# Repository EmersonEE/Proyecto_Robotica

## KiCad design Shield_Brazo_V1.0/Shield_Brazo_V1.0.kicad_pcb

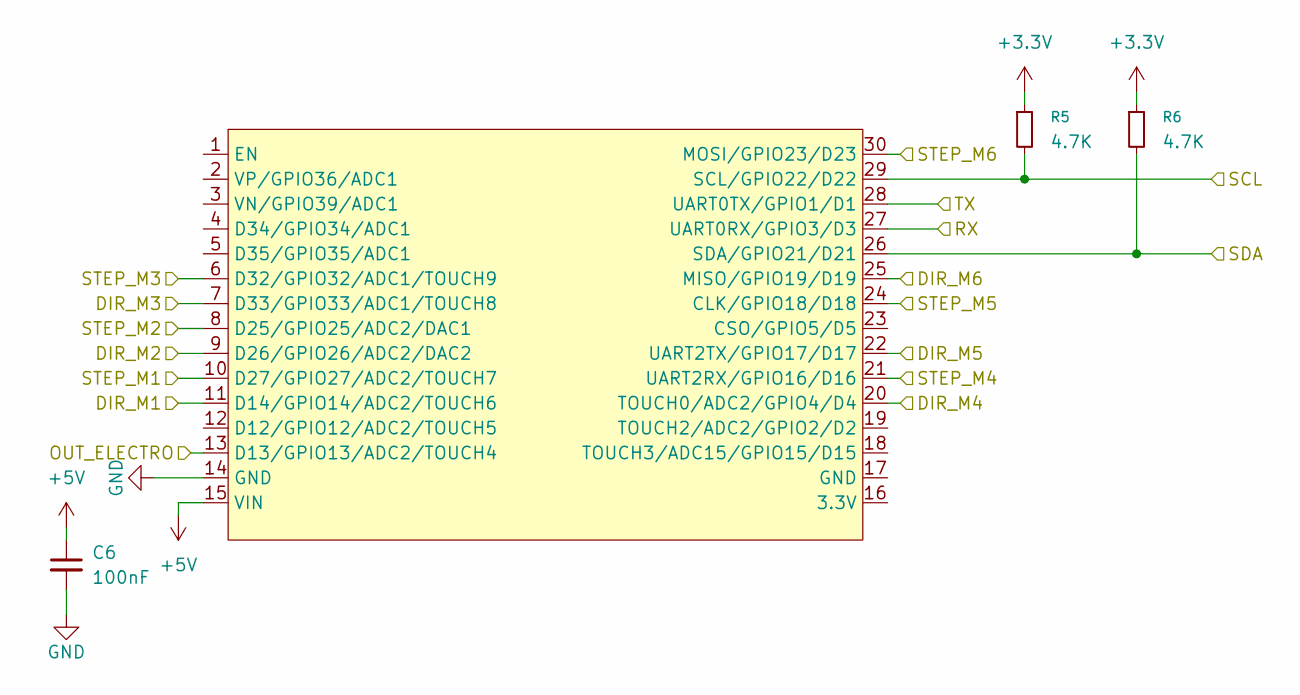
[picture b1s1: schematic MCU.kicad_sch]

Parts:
C6: 100nF; C_1206_3216Metric_Pad1.33x1.80mm_HandSolder
R5, R6: 4.7K
U6: ESP32_DevKit_V1_DOIT; ESP32_DEVKIT_V1_E32

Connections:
+3.3V: R5.1, R6.1; also elsewhere on the board
+5V: C6.1, U6.15 (VIN); also elsewhere on the board
/Drivers/DIR_M1: U6.11 (D14/GPIO14/ADC2/TOUCH6); also elsewhere on the board
/Drivers/DIR_M2: U6.9 (D26/GPIO26/ADC2/DAC2); also elsewhere on the board
/Drivers/DIR_M3: U6.7 (D33/GPIO33/ADC1/TOUCH8); also elsewhere on the board
/Drivers/DIR_M4: U6.20 (TOUCH0/ADC2/GPIO4/D4); also elsewhere on the board
/Drivers/DIR_M5: U6.22 (UART2TX/GPIO17/D17); also elsewhere on the board
/Drivers/DIR_M6: U6.25 (MISO/GPIO19/D19); also elsewhere on the board
/Drivers/STEP_M1: U6.10 (D27/GPIO27/ADC2/TOUCH7); also elsewhere on the board
/Drivers/STEP_M2: U6.8 (D25/GPIO25/ADC2/DAC1); also elsewhere on the board
/Drivers/STEP_M3: U6.6 (D32/GPIO32/ADC1/TOUCH9); also elsewhere on the board
/Drivers/STEP_M4: U6.21 (UART2RX/GPIO16/D16); also elsewhere on the board
/Drivers/STEP_M5: U6.24 (CLK/GPIO18/D18); also elsewhere on the board
/Drivers/STEP_M6: U6.30 (MOSI/GPIO23/D23); also elsewhere on the board
/MCU/OUT_ELECTRO: U6.13 (D13/GPIO13/ADC2/TOUCH4); also elsewhere on the board
/MCU/RX: U6.27 (UART0RX/GPIO3/D3); also elsewhere on the board
/MCU/SCL: R5.2, U6.29 (SCL/GPIO22/D22); also elsewhere on the board
/MCU/SDA: R6.2, U6.26 (SDA/GPIO21/D21); also elsewhere on the board
/MCU/TX: U6.28 (UART0TX/GPIO1/D1); also elsewhere on the board
GND: C6.2, U6.14 (GND); also elsewhere on the board

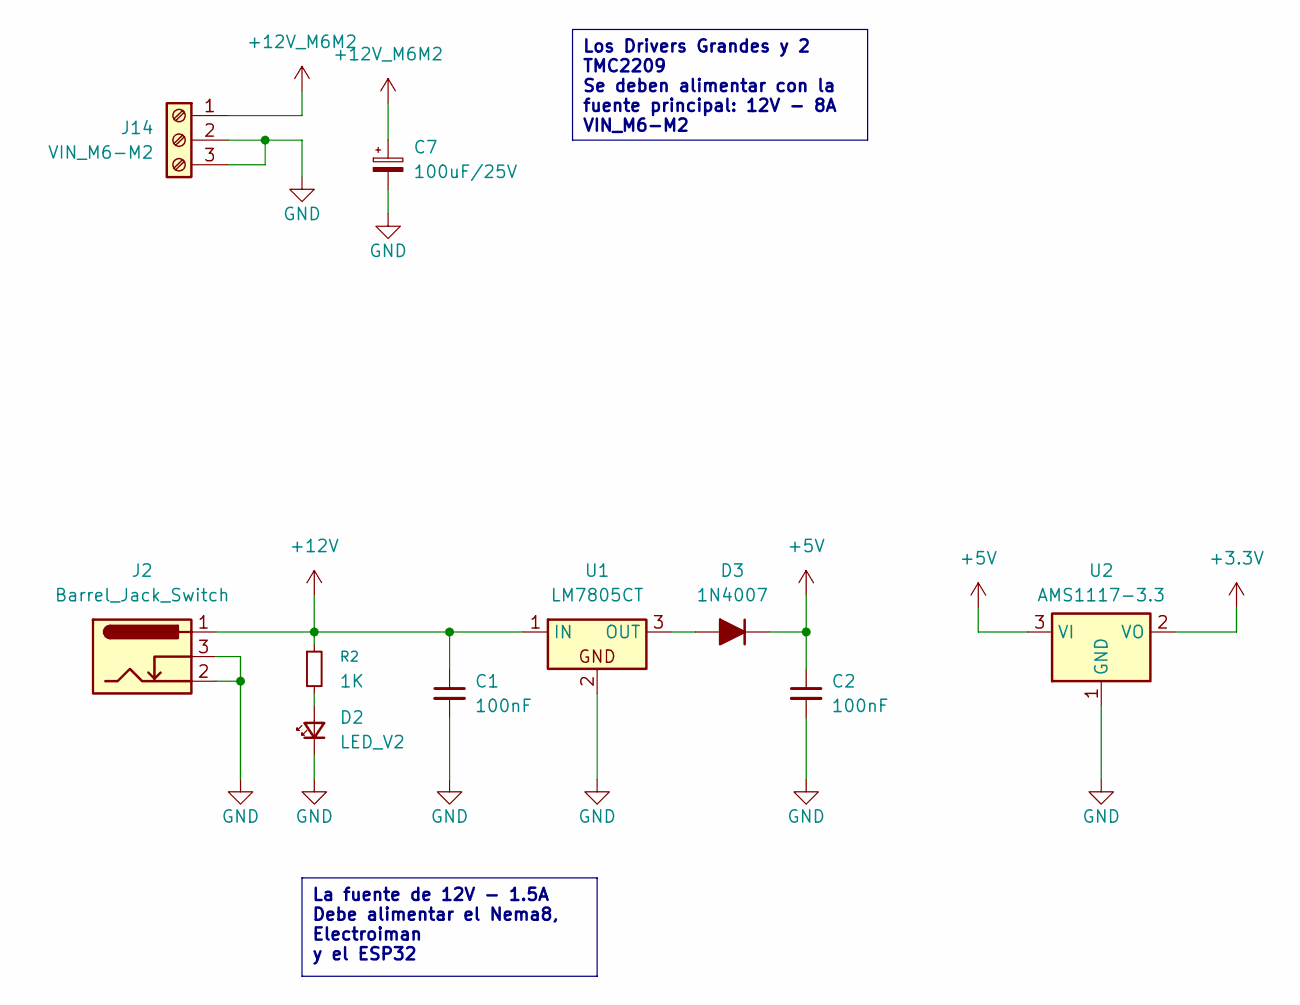
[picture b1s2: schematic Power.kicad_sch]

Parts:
C1, C2: 100nF; C_Disc_D4.7mm_W2.5mm_P5.00mm
C7: 100uF/25V; CP_Radial_D16.0mm_P7.50mm
D2: LED_V2; LED_D5.0mm
D3: 1N4007; D_DO-41_SOD81_P7.62mm_Horizontal
J2: Barrel_Jack_Switch; BarrelJack_GCT_DCJ200-10-A_Horizontal
J14: VIN_M6-M2; TerminalBlock_Phoenix_MKDS-1,5-3-5.08_1x03_P5.08mm_Horizont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
R2: 1K
U1: LM7805CT; TO-220-3_Horizontal_TabDown
U2: AMS1117-3.3; SOT-223-3_TabPin2

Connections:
+3.3V: U2.2 (VO); also elsewhere on the board
+5V: C2.1, D3.1 (K), U2.3 (VI); also elsewhere on the board
+12V: C1.1, J2.1, R2.1, U1.1 (IN); also elsewhere on the board
+12V_M6M2: C7.1, J14.1; also elsewhere on the board
GND: C1.2, C2.2, C7.2, D2.1 (K), J2.2, J2.3, J14.2, J14.3, U1.2, U2.1 (GND); also elsewhere on the board
unnamed: D2.2 (A), R2.2
unnamed: D3.2 (A), U1.3 (OUT)

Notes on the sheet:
La fuente de 12V - 1.5A Debe alimentar el Nema8, Electroiman y el ESP32
Los Drivers Grandes y 2 TMC2209 Se deben alimentar con la fuente principal: 12V - 8A VIN_M6-M2

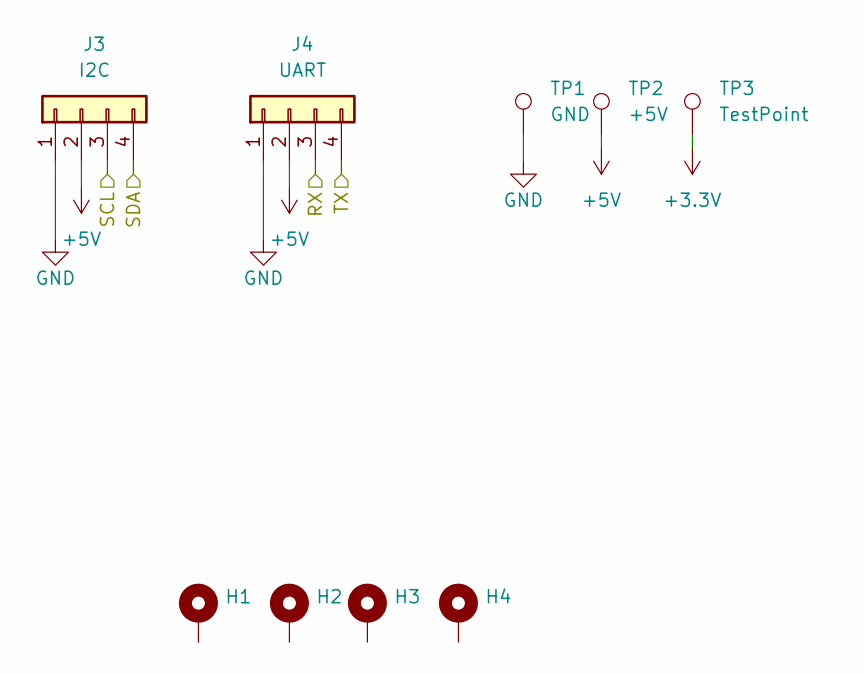
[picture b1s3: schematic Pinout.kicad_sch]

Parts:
H1, H2, H3, H4: MountingHole_3.2mm_M3_Pad_Via
J3: I2C; Molex_KK-254_AE-6410-04A_1x04_P2.54mm_Vertical
J4: UART; PinHeader_1x04_P2.54mm_Vertical
TP1: GND; TestPoint_Keystone_5005-5009_Compact
TP2: +5V; TestPoint_Keystone_5005-5009_Compact
TP3: TestPoint; TestPoint_Keystone_5005-5009_Compact

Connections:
+3.3V: TP3.1; also elsewhere on the board
+5V: J3.2, J4.2, TP2.1; also elsewhere on the board
/MCU/RX: J4.3; also elsewhere on the board
/MCU/SCL: J3.3; also elsewhere on the board
/MCU/SDA: J3.4; also elsewhere on the board
/MCU/TX: J4.4; also elsewhere on the board
GND: J3.1, J4.1, TP1.1; also elsewhere on the board

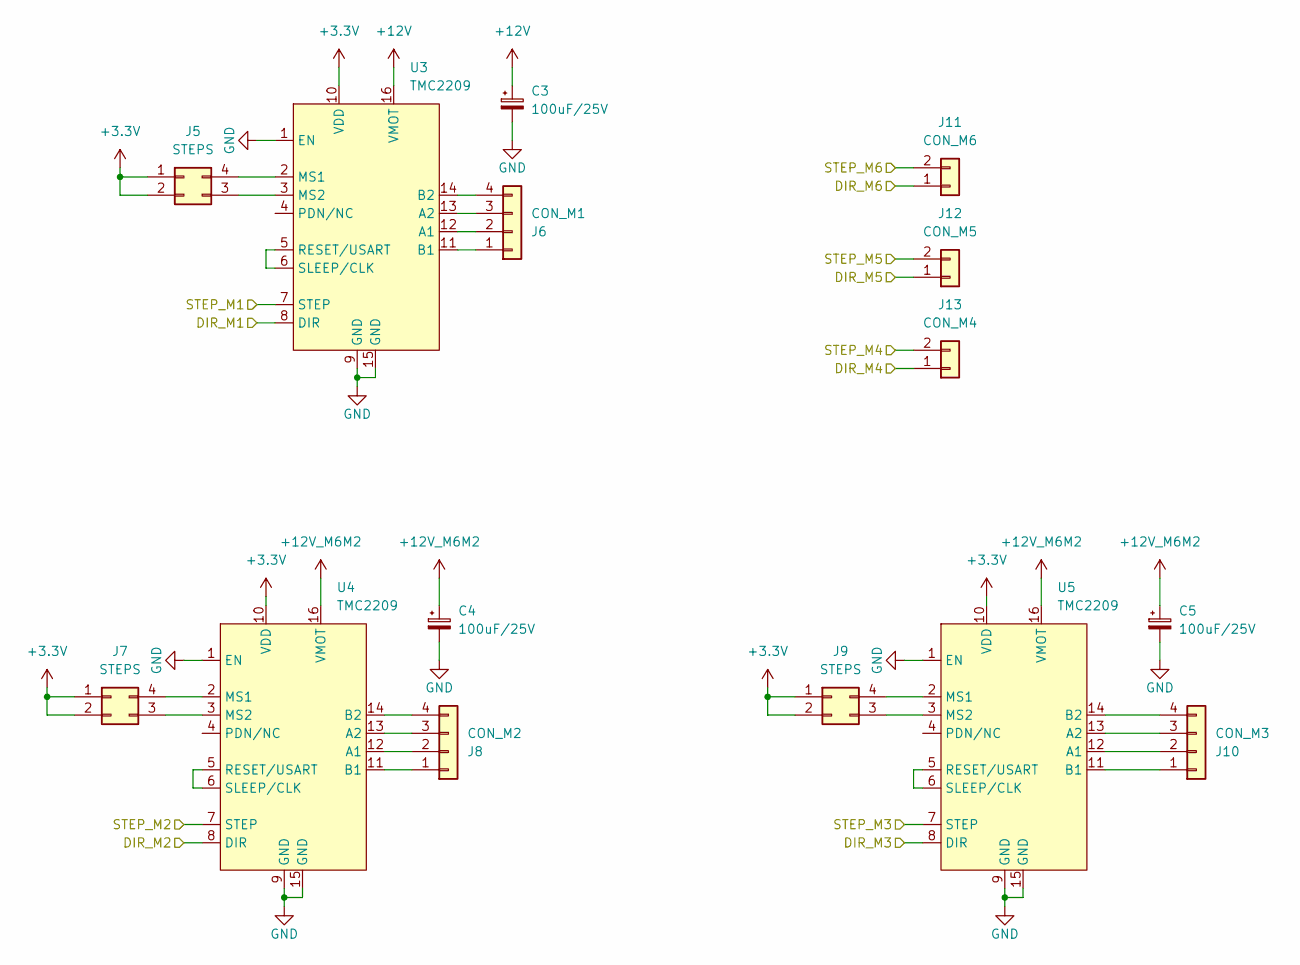
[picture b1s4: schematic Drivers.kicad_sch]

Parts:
C3, C4, C5: 100uF/25V; CP_Radial_D6.3mm_P2.50mm
J5, J7, J9: STEPS; PinHeader_2x02_P2.54mm_Vertical
J6: CON_M1; Molex_KK-254_AE-6410-04A_1x04_P2.54mm_Vertical
J8: CON_M2; Molex_KK-254_AE-6410-04A_1x04_P2.54mm_Vertical
J10: CON_M3; Molex_KK-254_AE-6410-04A_1x04_P2.54mm_Vertical
J11: CON_M6; Molex_KK-254_AE-6410-02A_1x02_P2.54mm_Vertical
J12: CON_M5; Molex_KK-254_AE-6410-02A_1x02_P2.54mm_Vertical
J13: CON_M4; Molex_KK-254_AE-6410-02A_1x02_P2.54mm_Vertical
U3, U4, U5: TMC2209

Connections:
+3.3V: J5.1, J5.2, J7.1, J7.2, J9.1, J9.2, U3.10 (VDD), U4.10 (VDD), U5.10 (VDD); also elsewhere on the board
+12V: C3.1, U3.16 (VMOT); also elsewhere on the board
+12V_M6M2: C4.1, C5.1, U4.16 (VMOT), U5.16 (VMOT); also elsewhere on the board
/Drivers/DIR_M1: U3.8 (DIR); also elsewhere on the board
/Drivers/DIR_M2: U4.8 (DIR); also elsewhere on the board
/Drivers/DIR_M3: U5.8 (DIR); also elsewhere on the board
/Drivers/DIR_M4: J13.1; also elsewhere on the board
/Drivers/DIR_M5: J12.1; also elsewhere on the board
/Drivers/DIR_M6: J11.1; also elsewhere on the board
/Drivers/STEP_M1: U3.7 (STEP); also elsewhere on the board
/Drivers/STEP_M2: U4.7 (STEP); also elsewhere on the board
/Drivers/STEP_M3: U5.7 (STEP); also elsewhere on the board
/Drivers/STEP_M4: J13.2; also elsewhere on the board
/Drivers/STEP_M5: J12.2; also elsewhere on the board
/Drivers/STEP_M6: J11.2; also elsewhere on the board
GND: C3.2, C4.2, C5.2, U3.1 (EN), U3.9 (GND), U3.15 (GND), U4.1 (EN), U4.9 (GND), U4.15 (GND), U5.1 (EN), U5.9 (GND), U5.15 (GND); also elsewhere on the board
unnamed: J5.3, U3.3 (MS2)
unnamed: J5.4, U3.2 (MS1)
unnamed: J6.1, U3.11 (B1)
unnamed: J6.2, U3.12 (A1)
unnamed: J6.3, U3.13 (A2)
unnamed: J6.4, U3.14 (B2)
unnamed: J7.3, U4.3 (MS2)
unnamed: J7.4, U4.2 (MS1)
unnamed: J8.1, U4.11 (B1)
unnamed: J8.2, U4.12 (A1)
unnamed: J8.3, U4.13 (A2)
unnamed: J8.4, U4.14 (B2)
unnamed: J9.3, U5.3 (MS2)
unnamed: J9.4, U5.2 (MS1)
unnamed: J10.1, U5.11 (B1)
unnamed: J10.2, U5.12 (A1)
unnamed: J10.3, U5.13 (A2)
unnamed: J10.4, U5.14 (B2)
unnamed: U3.5 (RESET/USART), U3.6 (SLEEP/CLK)
unnamed: U4.5 (RESET/USART), U4.6 (SLEEP/CLK)
unnamed: U5.5 (RESET/USART), U5.6 (SLEEP/CLK)

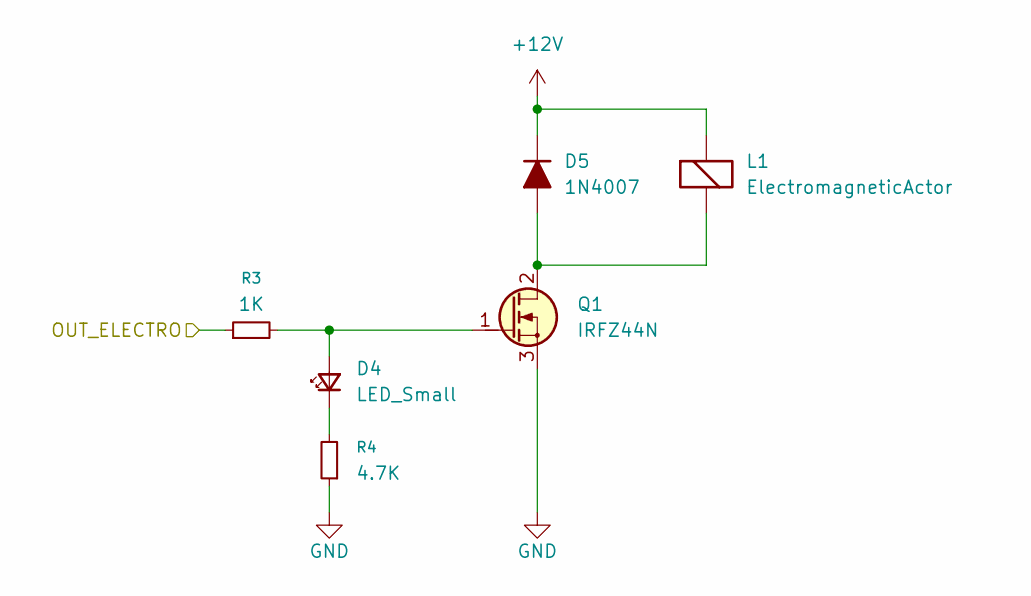
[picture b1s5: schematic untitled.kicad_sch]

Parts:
D4: LED_Small; LED_D3.0mm
D5: 1N4007; D_DO-41_SOD81_P7.62mm_Horizontal
L1: ElectromagneticActor; Molex_KK-254_AE-6410-02A_1x02_P2.54mm_Vertical
Q1: IRFZ44N; TO-220-3_VDC
R3: 1K
R4: 4.7K

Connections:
+12V: D5.1 (K), L1.1 (-); also elsewhere on the board
/MCU/OUT_ELECTRO: R3.1; also elsewhere on the board
GND: Q1.3 (S), R4.1; also elsewhere on the board
unnamed: D4.2 (A), Q1.1 (G), R3.2
unnamed: D4.1 (K), R4.2
unnamed: D5.2 (A), L1.2 (+), Q1.2 (D)

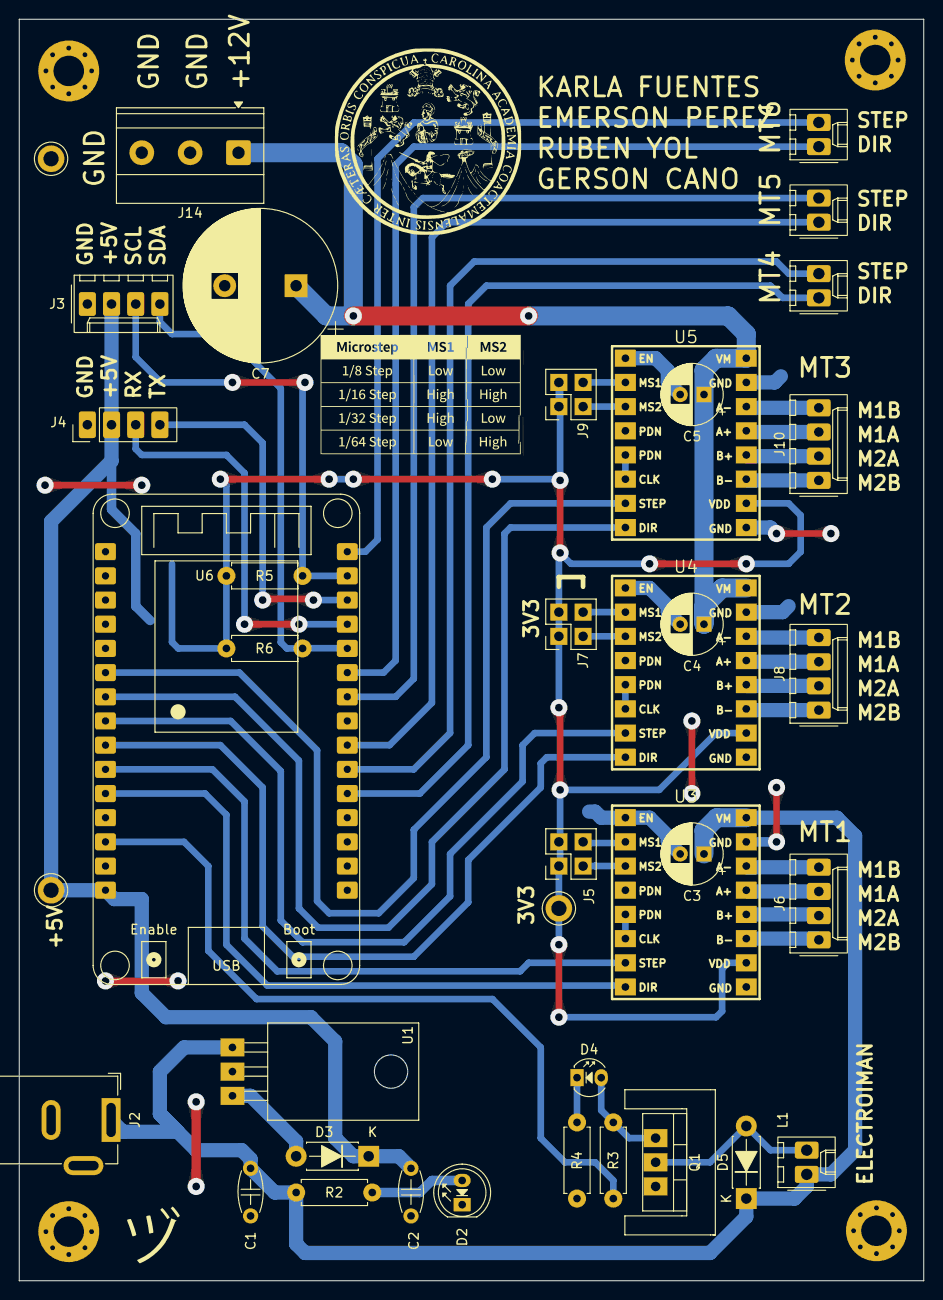
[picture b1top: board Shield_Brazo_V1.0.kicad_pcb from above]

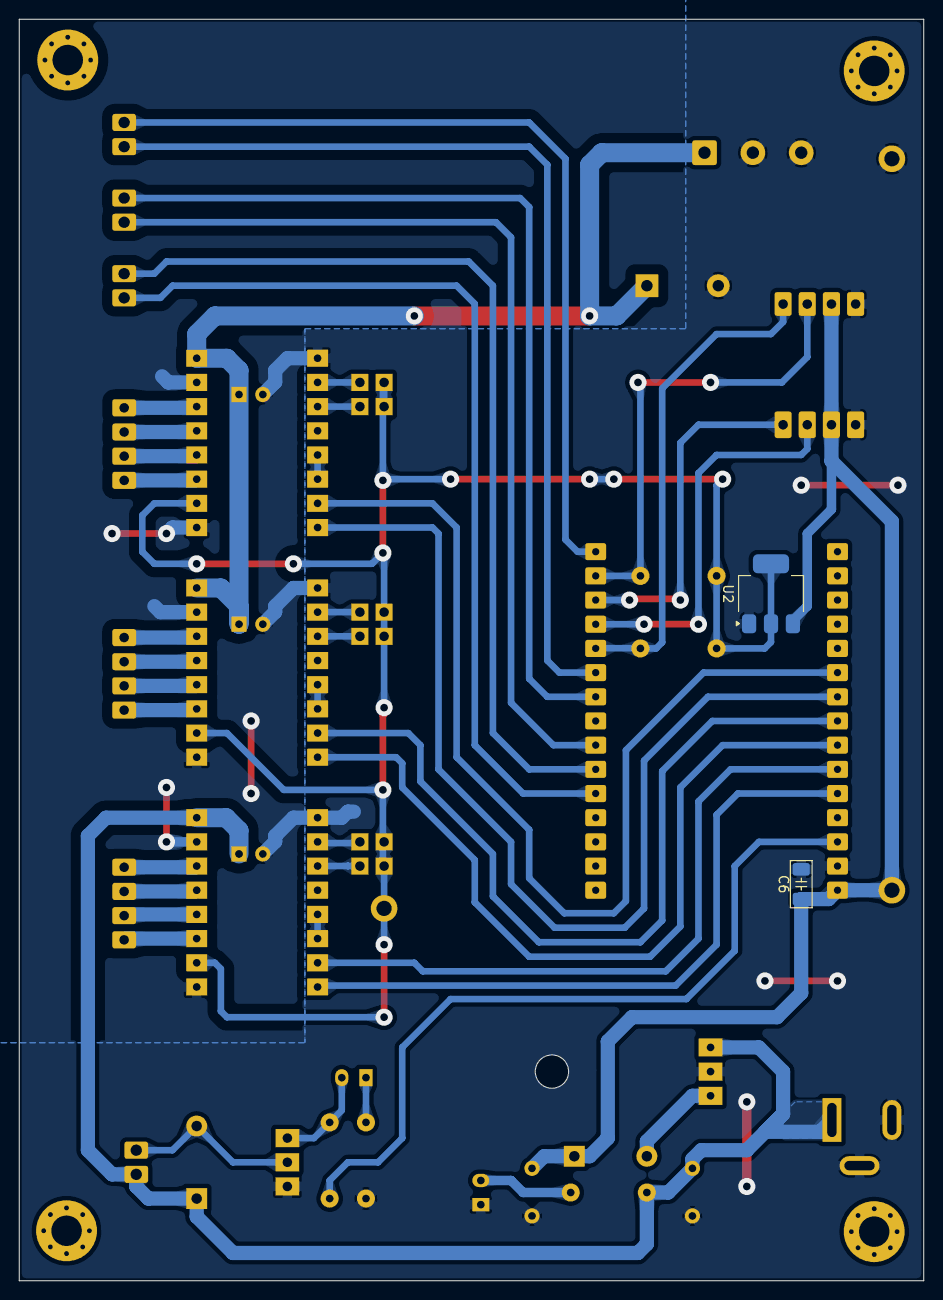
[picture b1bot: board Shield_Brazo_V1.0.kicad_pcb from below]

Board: 2 copper layers, 95.0 x 132.5 mm, 44 parts (2 on the bottom side), 48 nets.

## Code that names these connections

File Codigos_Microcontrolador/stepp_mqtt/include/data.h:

#include "sys/_intsup.h"
#include <Arduino.h>

const char *ssid = "CLARO_h9hU3j";
const char *password = "7474FB19FD";

const char *mqtt_server = "192.168.1.136";
const char *topic_sub = "/suscribirse";
const char *topic_pub = "/saludo";
const char *topic_electroiman = "/electroiman";
const char *topic_ws2812 = "/ws2812";
#define STEP_M1 27
#define DIR_M1 14

#define STEP_M2 25
#define DIR_M2 26

#define STEP_M3 32
#define DIR_M3 33

#define STEP_M4 4
#define DIR_M4 16

#define STEP_M5 17
#define DIR_M5 18

#define STEP_M6 19
#define DIR_M6 23

#define ELECTROIMAN 13
bool robotListo = false;

// int ordenMotores[6] = {5, 4, 3, 1, 2, 0};
int ordenMotores[6] = {4, 3, 1, 5, 2, 0};
const int DELAY_ENTRE_MOTORES = 20;
const long stepsPerRev[6] = {1600, 1600, 1600, 6400, 3200, 3200};
bool movimientoActivo = false;
float stepsPerDegree[6];

float posicionActual[6] = {0, 0, 0, 0, 0, 0};
bool ROBOT_LISTO = false;   // Se activará vía MQTT
bool homeRealizado = false; // Para asegurar que el Home solo ocurra una vez

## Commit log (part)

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2026-02-28 Inicio Proyecto
2026-02-28 Control-Manual
2026-02-28 Leyendo_Serial
2026-03-03 Activacion Electroiman
2026-03-03 Arduino-Robodk
2026-03-03 Leer Serial
2026-03-03 Serial Robodk
2026-03-05 Mqtt-Nemas-Serial
2026-03-05 mqtt-slider-serial
2026-03-05 Iniciando Proyecto PCB
2026-03-08 Terminada, Revision
2026-03-09 Electroiman
2026-03-09 Trayectorios_Individuales
2026-03-09 agregando tblock 3p
2026-03-16 Laptop
2026-03-17 Laptop2
2026-03-17 Laptop3
2026-03-20 Funcionando Electroiman Error
2026-04-15 Placa Terminada!
2026-04-15 Codigo Cerca
2026-05-09 Omarchy-RIP
